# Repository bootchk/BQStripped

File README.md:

##KiCad design files for a minimal circuit board using Texas Instruments part BQ25504 energy harvester.

Stripped means the voltage monitoring and battery management features of the BQ25504 are not used in the normal fashion.  Instead, if there is enough energy to harvest, the board charges the power out pins. Voltage out ranges from 0 to >6 volts. Typically used with a solar cell input and a tantalum capacitor output.

See the BQ25504 data sheet and solar example circuits.

Also shared at OSHPark (the tested Gerbers, i.e. the PDB fabrication files.)

(Also, I have another design which uses a load switch and programs VBAT_OK as control to the loadswitch so that output voltage switches on hard at say 1.9V and limits output voltage to 3.6V (the specs for a Nordic NRF52 radio chip.)  The board is slightly larger.  It uses the same sort of tricks to share resistor nets (which granted, are not that large in area.)  I would be glad to share that design also, but I haven't tested it yet.)

###Use Case

The BQ25504 (and thus the board) boosts voltage from small, low-voltage solar cells (panels) and also provides MPPT to optimize power extraction from the solar cell.

You don’t need this board if you don’t need either of those two functions.  For example if you use a solar panel with enough cells to give you enough voltage, and if your downstream voltage monitoring keeps the storage voltage near the solar panels MPP voltage (where it delivers the most power.)

###More on Stripped Design

The design programs the under-voltage, over-voltage, over-temperature, and in-regulation (VBAT_OK) thresholds to extremes by connecting various BQ25504 pins to ground or VRDIV.  This saves board space, by omitting resistor nets normally used to program the thresholds. For example, under voltage threshold is programmed to zero, and over voltage threshold is programmed much greater than the chips maximum rated voltage.

Typically you use a downstream, separate voltage monitor and/or regulator.  Typically, your downstream avoids draining storage below 1.8V (VCHGEN) so the BQ25504 does not enter coldstart, where it provides very little power.

###Interface

The board has power-in and power-out.  For power-in, there are two pairs of pins: a pair of through holes and a pair of pads on the back.  For power-out, there are three pairs of pins: two pairs of through hole and one pair of pads on the back.  Some of the pairs are optional, you can choose which to use.

The power-in pads accept a small, 5mm SMD photodiode (e.g. TEMD5080) used as a solar cell (which is a smallish solar cell that, in full sun, provides some power) if you want a solar cell on this board.  Often, you wire on a larger solar cell.

The power-out pads accept a small SMD capacitor, say in 3528 metric package, if you want storage on this board.

The third set of power-out pins exist to connect your load to the board (as well as connecting storage to the board.)

###Storage

You must provide storage, typically a capacitor greater than 0.1mF.  See the BQ25504 data sheet under “Choosing components.” Typical storage is a tantalum or super capacitor.

The board does NOT include a small, ceramic capacitor across power out, which might be needed to reduce ripple on power-out.

###Cautions

Since the battery management functions are not used, you should not use a chemical battery for storage without careful consideration of the possible consequences:
- low battery life due to undercharging
- risk of fire due to overcharging.

###BOM

You can generate one from the KiCad files.  See the BQ25504 data sheet for other suggestions.  Lands for the discretes are for 603 packages.  Lands for inductor L1 are for a part made by Wurth.

###Images

In the repository are:

  - PDF of schematic
  - PNG image of the front of the PCB (but its not pretty enough to help much in placing parts.)

###About the design

Certain pins of the BQ chip 'sample' resistor nets to program the chip's voltage regulation functions.  The reference designs from TI use separate resistor nets for each 'program'.  But you can share one resistor net among 'programs.'  That saves board space, but might limit the results of the programs (given the constraint that each resistor net must add up to say 10 meg ohm.)  Here, I eliminate the resistor nets altogether and connect the programming pins directory to reference voltages for the programming nets (VRDIV and ground.)  In the schematic, see the network labelel "High Prog", and the fact that the VBAT_OV pin is grounded.

For more information about these tricks, on the net is a presentation by the chip designer, where you can find a schematic for chip internals with respect to these programming pins.  Also, there is some discussion in the TI forums.

Note this design still has a resistor net for MPPT programming.  In my opinion, thats a waste also, since very few users will program MPPT to other than a rough value of 80% (of the solar cell's Voc.)

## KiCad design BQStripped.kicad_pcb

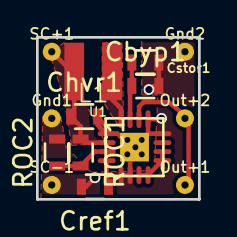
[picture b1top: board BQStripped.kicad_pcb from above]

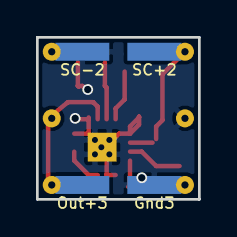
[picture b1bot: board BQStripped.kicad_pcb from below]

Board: 2 copper layers, 9.0 x 9.0 mm, 18 parts (4 on the bottom side), 8 nets.

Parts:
Cbyp1: 0.01uF; R_0603
Chvr1: 4.7uF; R_0603
Cref1: 0.01uF; R_0603
Cstor1: 4.7uF; R_0603
Gnd1: M-; TH400nm
Gnd2: CONN_01X01; TH400nm
Gnd3: CONN_01X01; 1x3mmPad
L1: 22uH; Wurth2828
Out+1: Bat; TH400nm
Out+2: M+; TH400nm
Out+3: M+; 1x3mmPad
ROC1, ROC2: R; R_0603
SC+1: CONN_01X01; TH400nm
SC+2: CONN_01X01; 1x3mmPad
SC-1: CONN_01X01; TH400nm
SC-2: CONN_01X01; 1x3mmPad
U1: BQ25504; QFN16thermalpasted

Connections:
GNDPWR: Cbyp1.2, Chvr1.2, Cref1.2, Cstor1.2, Gnd1.1, Gnd2.1, Gnd3.1, ROC2.2, SC-1.1, SC-2.1, U1.1, U1.5, U1.6, U1.12, U1.13, U1.17
HighProg: U1.7, U1.8, U1.9, U1.10
bat: Out+1.1, Out+2.1, Out+3.1, U1.14
lbst: L1.1, U1.16
mppt: ROC1.2, ROC2.1, U1.3
vin: Chvr1.1, L1.2, ROC1.1, SC+1.1, SC+2.1, U1.2
vref: Cref1.1, U1.4
vstor: Cbyp1.1, Cstor1.1, U1.15

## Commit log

2017-03-31 Images and more comments.
2021-02-27 add to readme
